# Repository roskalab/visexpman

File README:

Vision Experiment Manager was developed in Botond Roska's lab in Friedrich Miescher Instiute and Institute of Molecular and Clinical Ophthalmology Basel from 2011.

Two Photon GUI Development Guide
~~~~~~~~~~~~~~~~~~~~~~~~~~~~~~~~

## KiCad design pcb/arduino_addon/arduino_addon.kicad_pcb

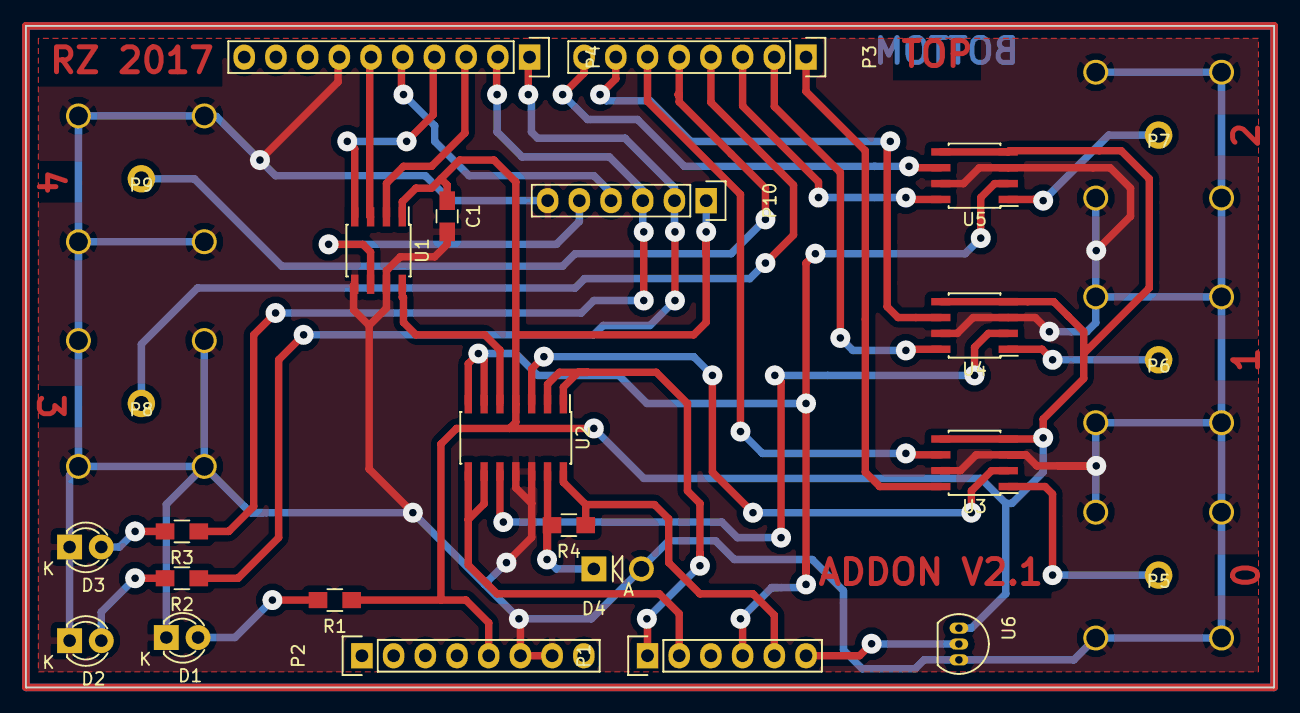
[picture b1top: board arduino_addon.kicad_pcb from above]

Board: 2 copper layers, 100.0 x 53.0 mm, 25 parts (0 on the bottom side), 32 nets.

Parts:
C1: 100n; C_0805_HandSoldering
D1, D2, D3: LED; LED-3MM
D4: photodiode; Diode_DO-41_SOD81_Vertical_AnodeUp
P1: AnalogIn; Pin_Header_Straight_1x06
P2: Power; Pin_Header_Straight_1x08
P3: Digital1; Pin_Header_Straight_1x08
P4: Digital2; Pin_Header_Straight_1x10
P5, P6, P7, P8, P9: BNC; bnc
P10: CONN_01X06; Pin_Header_Straight_1x06
R1, R2, R3: 330; R_0805_HandSoldering
R4: 47k; R_0805_HandSoldering
U1: MCP4812; SOIC-8_3.9x4.9mm_Pitch1.27mm
U2: LM324; SOIC-14_3.9x8.7mm_Pitch1.27mm
U3, U4, U5: ADG419; SOIC-8_3.9x4.9mm_Pitch1.27mm
U6: MCP9700T-E/TT; TO-92_Inline_Narrow_Oval

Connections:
+5V: C1.1, P2.5, P10.1, R1.1, U1.1, U2.4, U3.4, U3.5, U4.4, U4.5, U5.4, U5.5, U6.1
/AD0: P1.1, U2.1, U2.2
/AD1: P1.2, U2.8, U2.9
/AD4: P1.5, R4.1, U2.14
/AD5: P1.6, U6.2
/AI0: U2.3, U3.2
/AI1: U2.10, U4.2
/BNC0: P5.1, U3.1
/BNC1: P6.1, U4.1
/BNC2: P7.1, U5.1
/D0: P3.1, U3.8
/D1: P3.2, U4.8
/D2: P3.3, U5.8
/D3: P3.4, P8.1
/D4: P3.5, P9.1
/D5: P3.6, U3.6
/D6: P3.7, U4.6
/D7: P3.8, U5.6
/D8: P4.1, P10.2, R2.1
/D9: P4.2, P10.3, R3.1
/D10: P4.3, U1.2
/D11: P4.4, U1.4
/D12: P4.5, P10.4
/D13: P4.6, U1.3
/DAC0: P1.4, U2.6, U2.7, U5.2
/DAC1: P10.5, U1.6
GND: C1.2, D1.1, D2.1, D3.1, D4.2, P2.6, P2.7, P4.7, P5.2, P6.2, P7.2, P8.2, P9.2, P10.6, U1.5, U1.7, U2.11, U2.12, U3.3, U3.7, U4.3, U4.7, U5.3, U5.7, U6.3
unnamed: D1.2, R1.2
unnamed: D2.2, R2.2
unnamed: D3.2, R3.2
unnamed: D4.1, R4.2, U2.13
unnamed: U1.8, U2.5

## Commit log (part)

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2019-07-14 Video stimulus bugfix
2019-07-15 minor modification
2019-07-17 counter based trigger detection bugfixes
2019-07-22 miniscope datafolder is saved to behav video file (not tested)
2019-07-22 Error raised when daq device is not present
2019-07-23 pump control module (not tested)
2019-07-26 read stimulus video length updated (not tested)
2019-07-29 erg platform experiment start/stop works
2019-07-30 Two photon software: signal generation and GUI is ready
2019-07-30 bugfixes but polar plot and automated block/empty does not work yet
2019-07-31 polar plots opened after elphys recordings
2019-08-01 function for extracting elphys repetitions from traces
2019-08-06 minor updates
2019-08-15 Waveform generation fix, imaging data file implementation started
    Y signal ramp-up phase changed to linear from stepped
    Bux fix in plot function
    Every sawtooth signal extreme values were present twice - fixed
    Added experimental version of *.hdf5 file managing for the imaging data
    GUI improved in order to display previously recorded video frames from *.hdf5 file - with preview support
2019-08-17 Backup before AO/AI synchronization
2019-08-21 camera gui bugfix
2019-08-30 IR image added, ZMQ, Z-stack incomplete
    IR image added (via blue channel) with customizable position, rotation, etc., layers can be toggled.
    ZMQ support, functions being modified for remote control, not tested.
    Added FPS counter (for scan, not for update_image) in the bottom right corner. Visible during scanning.
    Started implementing Z stack, not finished yet.
2019-09-06 IR camera udp reader added (not tested)
2019-09-20 2p bugfixes (not complete)
2019-09-20 experiment start timestamp saved to datafile
2019-09-25 minor modifications
2019-09-26 receptive field angle correction seems to work
2019-09-26 2p: daq init (not ready)
2019-10-04 on GUI name field's name is configurable
2019-10-11 output folder can be selected from GUI
2019-10-18 2p modifications (not ready)
2019-10-23 Video stimulus: half frame rate playback option
2019-10-26 usb-uart sendbreak command does not block
2019-11-01 support for psychopy stim
2019-11-25 tile scan supported
2019-11-29 Stimulus tester works on Python 3.8
2019-12-11 mesc file reader
2019-12-30 Fixed bug in hdf5io when saving byte stream. Refactored hdf5io testing into separate module under tests. Other minor fixes and refactoring.
2020-01-07 fixed bug when collecting curves in align.py (line 399).
2020-01-20 screen angle calculation in config
2020-02-05 python3 compatibility modification
2020-03-23 gui engine test waveform
2020-03-31 Bugfix in displaying batch experiment setting
2020-04-01 Visexp GUI blocks experiment start if free space drops below 30 GB, camera GUI saves to mp4 (not tested)
2020-04-20 install script updated
2020-04-20 two photon: GUI restructured (not complete)
2020-04-26 SyncAnalogIO class (not tested)
2020-04-29 Scanner control: logging reworked, Thorlabs camera interface+recorder process
2020-05-01 image merge and filter functions
2020-05-01 image merge integrated into 2p GUI, bugfixes
2020-05-20 hdf5 handling bugfix
2020-05-22 z stack implemented but not tested
2020-05-27 image merge unittest (not complete)
2020-06-01 image merge unittest works, offset handling fixed for bigger 2p images
2020-06-03 z stack works, also saving to 3 different formats, daq and camera error display, displayed image aspect ratio is correct now
2020-06-06 free space warning parameter
2020-06-06 minor bugfixes in unittests
2020-06-30 minimal test station: recording completes without error
2020-07-07 numpy indexing bugfix
2020-07-27 image concatenate helper function
2020-07-28 create image grid function added
2020-08-04 cut image using a mask utility function
2020-08-15 2p: save snapshot
2020-09-02 Capture point on image by click helper function
2020-09-03 mc mea batch experiment bugfixes
2020-09-09 image display helpers
2020-09-16 fixed remaining imports
2020-09-18 generic platform added
2020-09-18 2p image display optimization
2020-09-18 2p image update minor optimization
2020-09-21 (WIP) Camera UI saves to mp4
2020-09-23 (WIP) Open ephys triggering
2020-09-25 scanner control bugfix
2020-09-28 2p image distortion bugfix
2020-09-29 gui engine modified
2020-09-30 (WIP) Migrate behavioral from python 2 to 3
2020-10-01 gui bugfix
2020-10-06 file trigger supported
2020-10-08 2p: shift setting and plot raw ai signal
2020-10-09 Qt5 compatibility modifications
2020-10-12 openphys files are zipped and moved to video file's folder
2020-10-14 openephys:file_quality_check draft
2020-10-15 os independent file path
2020-10-19 Behavioral python3 compatibility bugfixes
2020-10-23 stimullation_library: show_shapes2
2020-10-24 stimullation_library: show_shapes2 remove RGB color format support
2020-10-26 angle2pixel, get_grid added
2020-11-04 points_deg_to_distance_pix
2020-11-04 get grid coordinate order fixed
2020-11-05 grid 0.5 el eltolva, xy coordinates swapped
2020-11-07 object to numpy utility function
2020-11-09 minor updatesmerging code with smart setup #2
2020-11-11 typos
2020-11-11 junk files removed
2020-11-11 *.npy added to gitignore
2020-11-19 show_image() mask function
2020-11-20 generic platform related bugfixes
2020-11-30 Clear task after analog input read in order to make the device available for the next acquisition
2020-12-01 process icon added
2020-12-02 AnalogRecorder process cleanup+stop functions+moved to daq.py
2020-12-05 pth file added
2020-12-12 add abort function in analog read
2020-12-15 video aligned (WIP)
2020-12-16 Ignore exceptions on ai read abort (when called on a task which is not running). Since isTaskCompleted is not exposed in pyDAQmx, this is the simplest way to do it (not a nice one though).
2021-01-05 extract central object from binary image
2021-01-14 behavioral and eye camera video aligner
2021-01-15 placing points on image
2021-01-21 Read frame from video optimized
2021-02-01 MC MEA file triggering in camera GUI, start/stop recording refactoring
2021-02-05 Camera GUI handles UDP stop trigger
2021-02-08 MC MEA file triggering in camera GUI
2021-02-13 plot utility function in GUI, compare recorded frames with number of pulses
2021-02-18 camera bugfix
2021-02-18 MC MEA file triggering bugfix
2021-02-19 Visexpman GUI file triggering cleaned up
2021-03-05 Camera stop time reduced in Camera GUI
2021-03-15 camera gui: daq recording delay eliminated
2021-03-17 Improved LED tracking
2021-03-17 fUSI timing signal emulation
2021-03-22 two photon GUI bugfix
2021-03-24 Elphys command signal scaled display works, recording procedure works
2021-03-29 Voltage clamp works, scaling saved data
2021-03-30 Failsafe mode for mc_mea setup when stop trigger is not detected
2021-04-05 chirp stim bugfix
2021-04-13 Give warning when nvidia card not found
2021-04-13 Patch setup compatibility with PTB
2021-04-16 Emulated fusi timestamps
2021-04-20 PTB triggering bugfix
2021-04-22 migrating ao setup to Python3
2021-04-26 path recording bugfix
2021-05-03 uniblitz stim support
2021-05-28 IR led based head direction (WIP)
2021-05-28 TCP Server interface to MES/AO
2021-06-03 AO-MES socket based interface reworked, AO recording works but has to reconnect
2021-06-08 2p moving average
2021-06-16 click on image but don't draw roi
2021-06-16 eye camera format changed to mp4
2021-06-21 Gaussian blurred spot test stimulus
2021-06-24 2p: save to tiff, 2p image is rotated with 90 degree
2021-06-25 Neuropixels integrationű
2021-06-28 config bugfix
2021-06-30 Histogram eq and gamma filtering added to 2p
2021-07-14 move2zip pw support
2021-07-14 Hisotgram LUT added to 2p GUI
2021-07-19 Add experiment name to filename
2021-08-02 2p: ir zoom
2021-09-01 bugfix in saving machine config at ephys recordings
2021-09-02 Save video frames with correct orientation
2021-09-16 refactoring stimulus frame dump
2021-09-16 2p: smooth scanner signal, bugfix in file saving, camera: record second camera
2021-10-12 2p timelapse
2021-10-12 support MC experimenter file format
2021-10-13 2p bugfixes
2021-10-29 z stack timelapse
2021-11-03 z stack/timelapse bugfixes
2021-11-09 gui.Image option to display manual points concatenated
2021-11-23 2p signal reconstruction (WIP)
2021-11-30 Documentation update
2021-11-30 doc format renamed
2021-12-01 2p undistort finished, documented
2021-12-01 bitcode display on stimulus screen
2021-12-06 import error bugfixes
2021-12-08 2p bugfix, behavioral LEd based head direction calculation is more robust
2021-12-13 tutorial for implementing a recording GUI
2022-01-25 elphys trace display bugfix
2022-01-27 further steps in GUI development tutorial
2022-02-17 image inserted to tutorial
2022-02-21 saving time lapse z stack to tiff
2022-03-02 skip 2p undistortion when scanner signal is noisy
2022-03-29 stage control: set motion speed
2022-04-27 bitcode supported by showshape showgrating stimuli
2022-05-11 2p z stack merge bugfixes
2022-05-11 file save bugfix
2022-07-27 adopting camera gui to behavioral platform
2022-08-03 sync saved unscaled and scaled
2022-08-04 minor bugfix in displaying sync data
2022-08-12 diabling bitcode, gui engine: save config to output file
2022-08-16 2p improvements: stage speed increased, handle daq error during z stack, visualize z stack progress
2022-09-02 RTSI triggering support for NI DAQ card based 2p imaging
2022-10-22 digital io channel added
2022-10-22 digital IO additional channel
2022-11-23 image processing helper functions
2022-11-29 Live ephys signal scaling bugfix
2022-12-21 custom command handler in stim
2023-01-04 add deinit_stim_idle_command_handler
2023-01-16 refactoring PyQt5
2023-01-19 minor bugfix
2023-02-07 installer minor update
2023-02-08 check timing signals when recorded by elphys UI not stim
2023-03-10 Elphys LED stimulus visualization and data saving bugfix
2023-03-16 LED stimulus support, elphys parameters are streamlined
2023-03-23 waveplate control
2023-03-28 PMT tripping detection
2023-03-31 Update
    color.py es gui.py-nel elofordulo verziofrisetesek miatti elirasokat pusholtam:
    Qgui -> QWidget et csereltem, de csak ahol kellet es
    numpy.float -> float
2023-04-05 Checking 'enabled' state of motor
2023-04-08 Load and Storage check corrected
    [#ISSUE 44] A Tárhely és Terhelés ellenörzés problémát első körben megcsináltam. Készítettem egy jegyzőkönyvet amibe irogattam hogy milyen változtatásokat tettem a kódban. Linkeltem a docx fájlt.
2023-04-17 current clamp mode supported with LED stimulus
2023-04-20 elphys file opening bugfix
2023-04-21 enable common stimulus edit
2023-04-28 mac os compatibility bugfix
2023-05-23 QComboBox prefix added
2023-05-31 new icons added
2023-06-19 z stack timing fixed
2023-07-03 2p: waveplate homing disabled, z stack: stage speed adjustments
2023-07-13 2p: shutter enabling, z stack saves to ImageJ format, waveplate not initialized at startup
2023-07-13 PMT OFF-ON after trip
2023-09-04 safely terminate waveform generation
2023-09-18 icons
2023-09-19 retrive changes for further inspection -because engine/generic/gui.py and gui_engine.py
2023-09-20 Minor Python3 compatibility update
2023-09-20 daq: analog output clock bugfix
2023-09-25 elphys gui updates
2023-09-26 Support displaying no pulse stims
2023-10-04 elphys gui icon update
2023-10-07 viewall icon added
2023-10-26 Gui.py: update_curves() - autodownscale
2023-11-01 New icons for saving/loading
2023-11-08 update_fw icon for maxwell gui
2023-11-14 qt plot legend bugfix
2023-12-20 return folder name at creating not existing folder|
2023-12-20 2p: support full IR image resolution
2024-01-15 [IOP_recorder] pyqtgraph modification update
2024-02-26 annulus stimulus with color
